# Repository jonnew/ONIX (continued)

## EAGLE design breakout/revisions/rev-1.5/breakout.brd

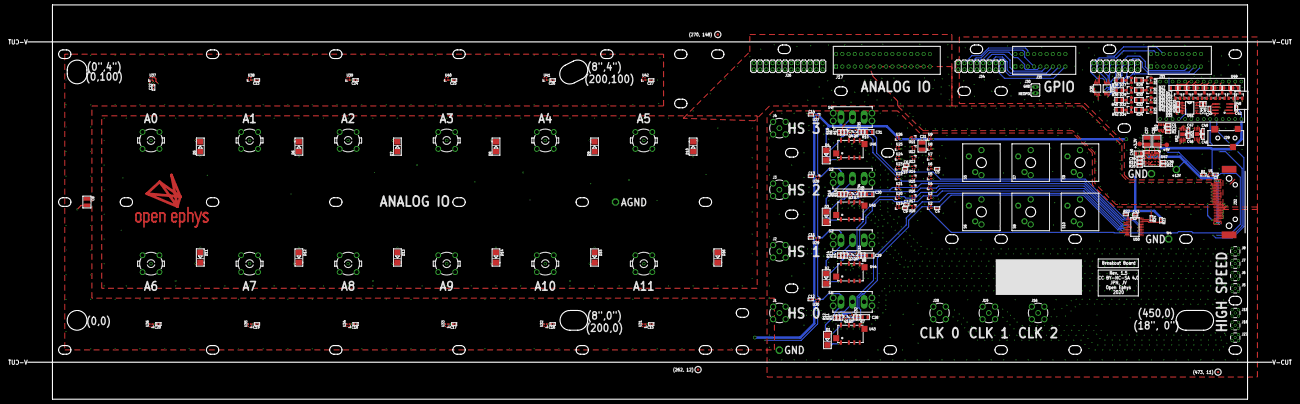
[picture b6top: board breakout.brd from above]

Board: 4 copper layers, 505.0 x 160.0 mm, 242 parts (0 on the bottom side), 165 nets.

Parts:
C1, C2, C3, C4, C5, C6, C7, C9, C10, C11, C12, C13, C14, C15, C16, C17, C18, C19, C20, C22, C23, C24, C25, C26, C27, C38, C39, C41, C42, C43, C45, C47, C49: 0.1uF; 0402
C8, C21, C36, C37: 47uF; 1210
C28, C29, C30, C31, C40: 10uF; 0805
C32, C33, C34, C35: 47nF; 0402
C44, C46, C48: 4.7nF; 0402
D1, D2, D3, D4: S1GTR; SMA-DO214AC
D5, D6, D7, D8, D9, D10, D11, D12, D13, D14, D15, D16: P6SMB18CA; SMA-DO214AC
D17, D18, D19, D20, D22, D23, D24, D25, D26, D27, D28, D29, D31, D32, D33, D34: BAT54SLT1G; SOT23
D21, D30: CM1213−08MR; MSOP-10-3X3
E$1, E$3, E$5: FIDUCIAL
J1, J2, J3, J4, J16, J19, J28: SMA_JACK_142-0701-201
J5, J6, J7, J8, J15, J18, J27: MMCX-THRU
J9, J10, J11, J12, J13, J14, J20, J21, J22, J23, J24, J25: 0731010360
J17: 1789074; SCREW16-2
J26: 69168-124HLF; 2X12-BIG
J29: SJ1-3514-SMT-TR; 35RASMT2BHNTRX
J30: JP2
J31, J34: 69168-116HLF; 2X08-BIG
J32: 12226-8250-00FR; 12226-82X0-00XX
J33, J35: 1888276; SCREW9-2
Q1, Q2, Q3, Q4, Q5, Q6, Q7, Q8: SI1012R; SC75
R1: 500; 0402
R2, R22, R23, R24: 4.7k; 0402
R3, R4, R5, R6, R11, R13, R15, R17: 1k; 0402
R7, R8, R9, R10: 49.9; 0402
R12, R14, R16, R18: 100k; 0402
R19: 13.3k; 0402
R20: 649k; 0402
R21: 8.25k; 0402
R25, R26: 100; 0402
R27, R28, R29, R30, R31, R32, R33, R34, R35, R36, R37, R38, R39, R40, R41, R42: 270, 0.5W; 0805
S1, S2, S3, S4: 7101J1V3BE2; CK_7101J1V3QE2
S5, S6, S7, S8, S9, S10: CHERRY-MX
TP1, TP2: TP19R
TP3, TP4, TP5, TP6, TP7: TESTPOINT_2MM
U1, U2, U3, U4, U5, U6, U7, U8, U9, U11, U12, U13, U14, U15, U16, U17, U18, U19, U20, U21, U22, U23, U24, U25, U26, U27, U28, U29, U30, U31, U32, U33, U34, U35, U36, U37, U38, U39, U40, U41, U42: SK6805-E-J; NEOPIXEL-1.5X1.5
U10: TXB0101; SOT23-6
U43, U44, U45, U46: G6K-2F-RF; G6KU-2F-RF
U47: LTM4622A; BGA_5X5_625X625
U48: SI8610; SO-08
U49: TINY-FPGA-BX; TINY-FPGA-BX_BASIC
U50: TCA9555; TSSOP-24
U51: FIN1032MTCX; TSSOP-16
U52, U53: SN65LVDS9638DGN; MSOP-8-PAD-3X3
X: OE-LOGO_28X20; OE-LOGO-28X20

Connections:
!TCA_INT: R22.2, U50.1
+3V3: C1.1, C37.2, C43.2, C44.1, C45.1, C46.1, C47.1, C48.1, C49.1, D17.2, D18.2, D19.2, D20.2, D21.8, D22.2, D23.2, D24.2, D25.2, D26.2, D27.2, D28.2, D29.2, D30.8, D31.2, D32.2, D33.2, D34.2, R2.1, R22.1, R23.1, R24.1, TP1.TP, U10.1, U47.D1, U47.E1, U50.24, U51.4, U51.16, U52.1, U53.1
+5V0: C2.1, C3.2, C4.2, C5.2, C6.2, C7.2, C8.2, C9.2, C10.2, C11.2, C12.2, C13.2, C14.2, C15.2, C16.2, C17.2, C18.2, C19.2, C20.2, C21.2, C22.2, C23.2, C24.2, C25.2, C26.2, C27.2, C36.2, C42.2, D1.C, D2.C, D3.C, D4.C, S1.3, S2.3, S3.3, S4.3, TP2.TP, U1.2, U2.2, U3.2, U4.2, U5.2, U6.2, U7.2, U8.2, U9.2, U10.6, U11.2, U12.2, U13.2, U14.2, U15.2, U16.2, U17.2, U18.2, U19.2, U20.2, U21.2, U22.2, U23.2, U24.2, U25.2, U26.2, U27.2, U28.2, U29.2, U30.2, U31.2, U32.2, U33.2, U34.2, U35.2, U36.2, U37.2, U38.2, U39.2, U40.2, U41.2, U42.2, U43.1, U44.1, U45.1, U46.1, U47.A1, U47.B1, U48.1, U49.VIN
+12V: C40.2, J32.1, J32.26, TP7.1, U47.A2, U47.B2, U47.B3, U47.D2, U47.D3, U47.E2
AGND: D5.A, D6.A, D7.A, D8.A, D9.A, D10.A, D11.A, D12.A, D13.A, D14.A, D15.A, D16.A, J9.2, J9.3, J9.4, J9.5, J10.2, J10.3, J10.4, J10.5, J11.2, J11.3, J11.4, J11.5, J12.2, J12.3, J12.4, J12.5, J13.2, J13.3, J13.4, J13.5, J14.2, J14.3, J14.4, J14.5, J17.1, J17.2, J17.15, J17.16, J17.17, J17.18, J17.31, J17.32, J20.2, J20.3, J20.4, J20.5, J21.2, J21.3, J21.4, J21.5, J22.2, J22.3, J22.4, J22.5, J23.2, J23.3, J23.4, J23.5, J24.2, J24.3, J24.4, J24.5, J25.2, J25.3, J25.4, J25.5, J26.1, J26.3, J26.5, J26.7, J26.9, J26.11, J26.13, J26.15, J26.17, J26.19, J26.21, J26.23, J32.13, J32.14, TP6.1
AIO_0: D5.C, J9.1, J17.3, J17.19, J26.2, J32.20
AIO_1: D6.C, J10.1, J17.4, J17.20, J26.4, J32.7
AIO_2: D7.C, J11.1, J17.5, J17.21, J26.6, J32.19
AIO_3: D8.C, J12.1, J17.6, J17.22, J26.8, J32.6
AIO_4: D9.C, J13.1, J17.7, J17.23, J26.10, J32.18
AIO_5: D10.C, J14.1, J17.8, J17.24, J26.12, J32.5
AIO_6: D11.C, J17.9, J17.25, J20.1, J26.14, J32.17
AIO_7: D12.C, J17.10, J17.26, J21.1, J26.16, J32.4
AIO_8: D13.C, J17.11, J17.27, J22.1, J26.18, J32.16
AIO_9: D14.C, J17.12, J17.28, J23.1, J26.20, J32.3
AIO_10: D15.C, J17.13, J17.29, J24.1, J26.22, J32.15
AIO_11: D16.C, J17.14, J17.30, J25.1, J26.24, J32.2
BUTTON0: S5.SW1, U50.16
BUTTON1: S7.SW1, U50.17
BUTTON2: S9.SW1, U50.18
BUTTON3: S6.SW1, U50.11
BUTTON4: S8.SW1, U50.14
BUTTON5: S10.SW1, U50.10
DIN0: D30.4, J34.2, J35.2, J35.11, R42.2
DIN0_P: D34.3, R42.1, U49.14
DIN1: D30.3, J34.4, J35.3, J35.12, R34.2
DIN1_P: D25.3, R34.1, U49.15
DIN2: D30.2, J34.6, J35.4, J35.13, R40.2
DIN2_P: D32.3, R40.1, U49.16
DIN3: D30.1, J34.8, J35.5, J35.14, R32.2
DIN3_P: D23.3, R32.1, U49.9
DIN4: D30.10, J34.10, J35.6, J35.15, R38.2
DIN4_P: D29.3, R38.1, U49.10
DIN5: D30.9, J34.12, J35.7, J35.16, R30.2
DIN5_P: D20.3, R30.1, U49.11
DIN6: D30.7, J34.14, J35.8, J35.17, R36.2
DIN6_P: D27.3, R36.1, U49.12
DIN7: D30.6, J34.16, J35.9, J35.18, R28.2
DIN7_P: D18.3, R28.1, U49.13
DOUT0: D21.10, J31.2, J33.2, J33.11, R27.2
DOUT0_P: D17.3, R27.1, U49.8
DOUT1: D21.9, J31.4, J33.3, J33.12, R29.2
DOUT1_P: D19.3, R29.1, U49.7
DOUT2: D21.7, J31.6, J33.4, J33.13, R31.2
DOUT2_P: D22.3, R31.1, U49.6
DOUT3: D21.6, J31.8, J33.5, J33.14, R33.2
DOUT3_P: D24.3, R33.1, U49.5
DOUT4: D21.1, J31.10, J33.6, J33.15, R35.2
DOUT4_P: D26.3, R35.1, U49.4
DOUT5: D21.2, J31.12, J33.7, J33.16, R37.2
DOUT5_P: D28.3, R37.1, U49.3
DOUT6: D21.3, J31.14, J33.8, J33.17, R39.2
DOUT6_P: D31.3, R39.1, U49.2
DOUT7: D21.4, J31.16, J33.9, J33.18, R41.2
DOUT7_P: D33.3, R41.1, U49.1
GND: C1.2, C2.2, C3.1, C4.1, C5.1, C6.1, C7.1, C8.1, C9.1, C10.1, C11.1, C12.1, C13.1, C14.1, C15.1, C16.1, C17.1, C18.1, C19.1, C20.1, C21.1, C22.1, C23.1, C24.1, C25.1, C26.1, C27.1, C28.1, C29.1, C30.1, C31.1, C36.1, C37.1, C38.1, C39.1, C40.1, C42.1, C43.1, C44.2, C45.2, C46.2, C47.2, C48.2, C49.2, D17.1, D18.1, D19.1, D20.1, D21.5, D22.1, D23.1, D24.1, D25.1, D26.1, D27.1, D28.1, D29.1, D30.5, D31.1, D32.1, D33.1, D34.1, J1.GND$1, J1.GND$2, J1.GND$3, J1.GND$4, J2.GND$1, J2.GND$2, J2.GND$3, J2.GND$4, J3.GND$1, J3.GND$2, J3.GND$3, J3.GND$4, J4.GND$1, J4.GND$2, J4.GND$3, J4.GND$4, J5.GND@1, J5.GND@2, J5.GND@3, J5.GND@4, J6.GND@1, J6.GND@2, J6.GND@3, J6.GND@4, J7.GND@1, J7.GND@2, J7.GND@3, J7.GND@4, J8.GND@1, J8.GND@2, J8.GND@3, J8.GND@4, J15.GND@1, J15.GND@2, J15.GND@3, J15.GND@4, J16.GND$1, J16.GND$2, J16.GND$3, J16.GND$4, J18.GND@1, J18.GND@2, J18.GND@3, J18.GND@4, J19.GND$1, J19.GND$2, J19.GND$3, J19.GND$4, J27.GND@1, J27.GND@2, J27.GND@3, J27.GND@4, J28.GND$1, J28.GND$2, J28.GND$3, J28.GND$4, J30.2, J31.1, J31.3, J31.5, J31.7, J31.9, J31.11, J31.13, J31.15, J32.PAD1, J32.PAD2, J33.1, J33.10, J34.1, J34.3, J34.5, J34.7, J34.9, J34.11, J34.13, J34.15, J35.1, J35.10, Q5.2, Q6.2, Q7.2, Q8.2, R7.2, R8.2, R9.2, R10.2, R11.1, R12.1, R13.1, R14.1, R15.1, R16.1, R17.1, R18.1, R19.2, R20.2, R21.2, S1.2, S2.2, S3.2, S4.2, S5.SW2, S6.SW2, S7.SW2, S8.SW2, S9.SW2, S10.SW2, TP3.1, TP4.1, TP5.1, U1.4, U2.4, U3.4, U4.4, U5.4, U6.4, U7.4, U8.4, U9.4, U10.2, U11.4, U12.4, U13.4, U14.4, U15.4, U16.4, U17.4, U18.4, U19.4, U20.4, U21.4, U22.4, U23.4, U24.4, U25.4, U26.4, U27.4, U28.4, U29.4, U30.4, U31.4, U32.4, U33.4, U34.4, U35.4, U36.4, U37.4, U38.4, U39.4, U40.4, U41.4, U42.4, U43.CASE1, U43.CASE2, U44.CASE1, U44.CASE2, U45.CASE1, U45.CASE2, U46.CASE1, U46.CASE2, U47.B5, U47.C1, U47.C2, U47.C5, U47.D5, U48.4, U49.GND@1, U49.GND@2, U50.2, U50.3, U50.12, U50.21, U51.8, U51.9, U51.10, U51.12, U51.14, U51.15, U52.4, U52.PAD, U53.3, U53.4, U53.PAD
HARP_CLKOUT: U48.2, U49.24
I2C_SCL: R23.2, U49.23, U50.22
I2C_SDA: R24.2, U49.22, U50.23
LOCKED: U9.3, U11.1
LVDS_DIN0_N: J32.23, U52.5
LVDS_DIN0_P: J32.10, U52.6
LVDS_DIN1_N: J32.11, U52.7
LVDS_DIN1_P: J32.24, U52.8
LVDS_DIN2_N: J32.25, U53.7
LVDS_DIN2_P: J32.12, U53.8
LVDS_DOUT0_N: J32.8, R25.1, U51.1
LVDS_DOUT0_P: J32.21, R25.2, U51.2
LVDS_DOUT1_N: J32.9, R26.1, U51.7
LVDS_DOUT1_P: J32.22, R26.2, U51.6
LVDS_IN_0: U49.18, U51.3
LVDS_IN_1: U49.17, U51.5
LVDS_OUT_0: U49.19, U52.3
LVDS_OUT_1: U49.20, U52.2
LVDS_OUT_2: U49.21, U53.2
unnamed: J15.SIG, J16.CLK
unnamed: J18.SIG, J19.CLK
unnamed: J27.SIG, J28.CLK
unnamed: D1.A, Q1.3, U43.7
unnamed: Q1.2, Q5.3
unnamed: U11.3, U12.1
unnamed: U12.3, U13.1
unnamed: U13.3, U14.1
unnamed: U36.3, U37.1
unnamed: U31.3, U32.1
unnamed: D2.A, Q2.3, U44.7
unnamed: U15.3, U16.1
unnamed: U16.3, U17.1
unnamed: C32.2, U43.6
unnamed: C41.1, J29.1, U48.8
unnamed: C41.2, J29.5, U48.5
unnamed: J29.4, U48.6
unnamed: J6.SIG, U44.5
unnamed: U17.3, U18.1
unnamed: U1.3, U2.1
unnamed: C33.1, R8.1
unnamed: R3.1, S1.1
unnamed: R21.1, U47.A4
unnamed: R19.1, U47.E4
unnamed: C38.2, U47.A3
unnamed: C39.2, U47.E3
unnamed: J5.SIG, U43.5
unnamed: J1.CLK, U43.1X6
unnamed: C32.1, R7.1
unnamed: C33.2, U44.6
unnamed: Q3.2, Q7.3
unnamed: C34.1, R9.1
unnamed: J2.CLK, U44.1X6
unnamed: R4.2, S2.1
unnamed: C34.2, U45.6
unnamed: J7.SIG, U45.5
unnamed: R5.2, S3.1
unnamed: Q2.2, Q6.3
unnamed: U2.3, U3.1
unnamed: U3.3, U4.1
unnamed: J3.CLK, U45.1X6
unnamed: R6.2, S4.1
unnamed: C35.1, R10.1
unnamed: C35.2, U46.6
unnamed: J8.SIG, U46.5
unnamed: J4.CLK, U46.1X6
unnamed: U4.3, U5.1
unnamed: D3.A, Q3.3, U45.7
unnamed: U6.3, U7.1
unnamed: U7.3, U8.1
unnamed: U8.3, U9.1
unnamed: R1.2, U1.1
unnamed: R1.1, U10.4
unnamed: U5.3, U6.1
unnamed: R2.2, U10.5
unnamed: U14.3, U15.1
unnamed: D4.A, Q4.3, U46.7
unnamed: Q4.2, Q8.3
unnamed: U32.3, U33.1
unnamed: U33.3, U34.1
unnamed: U34.3, U35.1
unnamed: U35.3, U36.1
unnamed: U37.3, U38.1
unnamed: U38.3, U39.1
unnamed: U39.3, U40.1
unnamed: U40.3, U41.1
unnamed: U41.3, U42.1
unnamed: U18.3, U19.1
unnamed: U19.3, U20.1
unnamed: U20.3, U21.1
unnamed: U21.3, U22.1
unnamed: U22.3, U23.1
unnamed: U23.3, U24.1
unnamed: U24.3, U25.1
unnamed: U25.3, U26.1
unnamed: U26.3, U27.1
unnamed: U27.3, U28.1
unnamed: U28.3, U29.1
unnamed: U29.3, U30.1
unnamed: U30.3, U31.1
unnamed: R20.1, U47.C4
NEOPIXEL_DIN: J30.1, U10.3
RELAY_AND_0: Q5.1, R11.2, U50.8
RELAY_AND_1: Q6.1, R13.2, U50.6
RELAY_AND_2: Q7.1, R15.2, U50.4
RELAY_AND_3: Q8.1, R17.2, U50.20
RELAY_MECH_0: C28.2, Q1.1, R3.2, R12.2, U50.9
RELAY_MECH_1: C29.2, Q2.1, R4.1, R14.2, U50.7
RELAY_MECH_2: C30.2, Q3.1, R5.1, R16.2, U50.5
RELAY_MECH_3: C31.2, Q4.1, R6.1, R18.2, U50.19
